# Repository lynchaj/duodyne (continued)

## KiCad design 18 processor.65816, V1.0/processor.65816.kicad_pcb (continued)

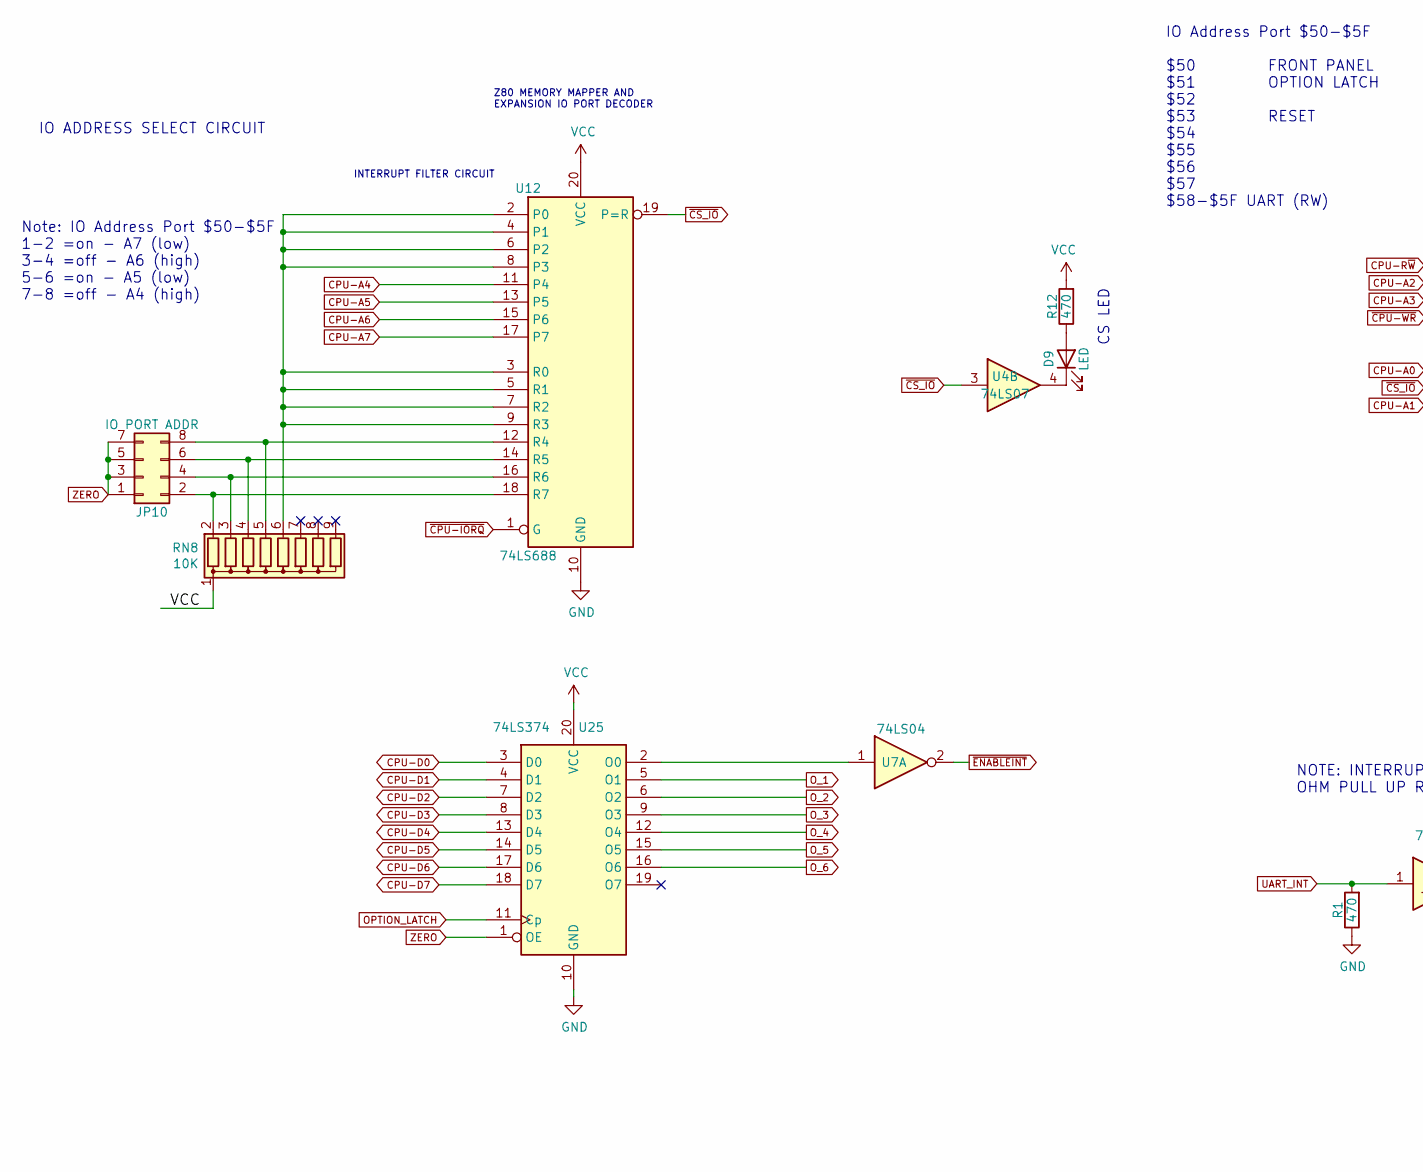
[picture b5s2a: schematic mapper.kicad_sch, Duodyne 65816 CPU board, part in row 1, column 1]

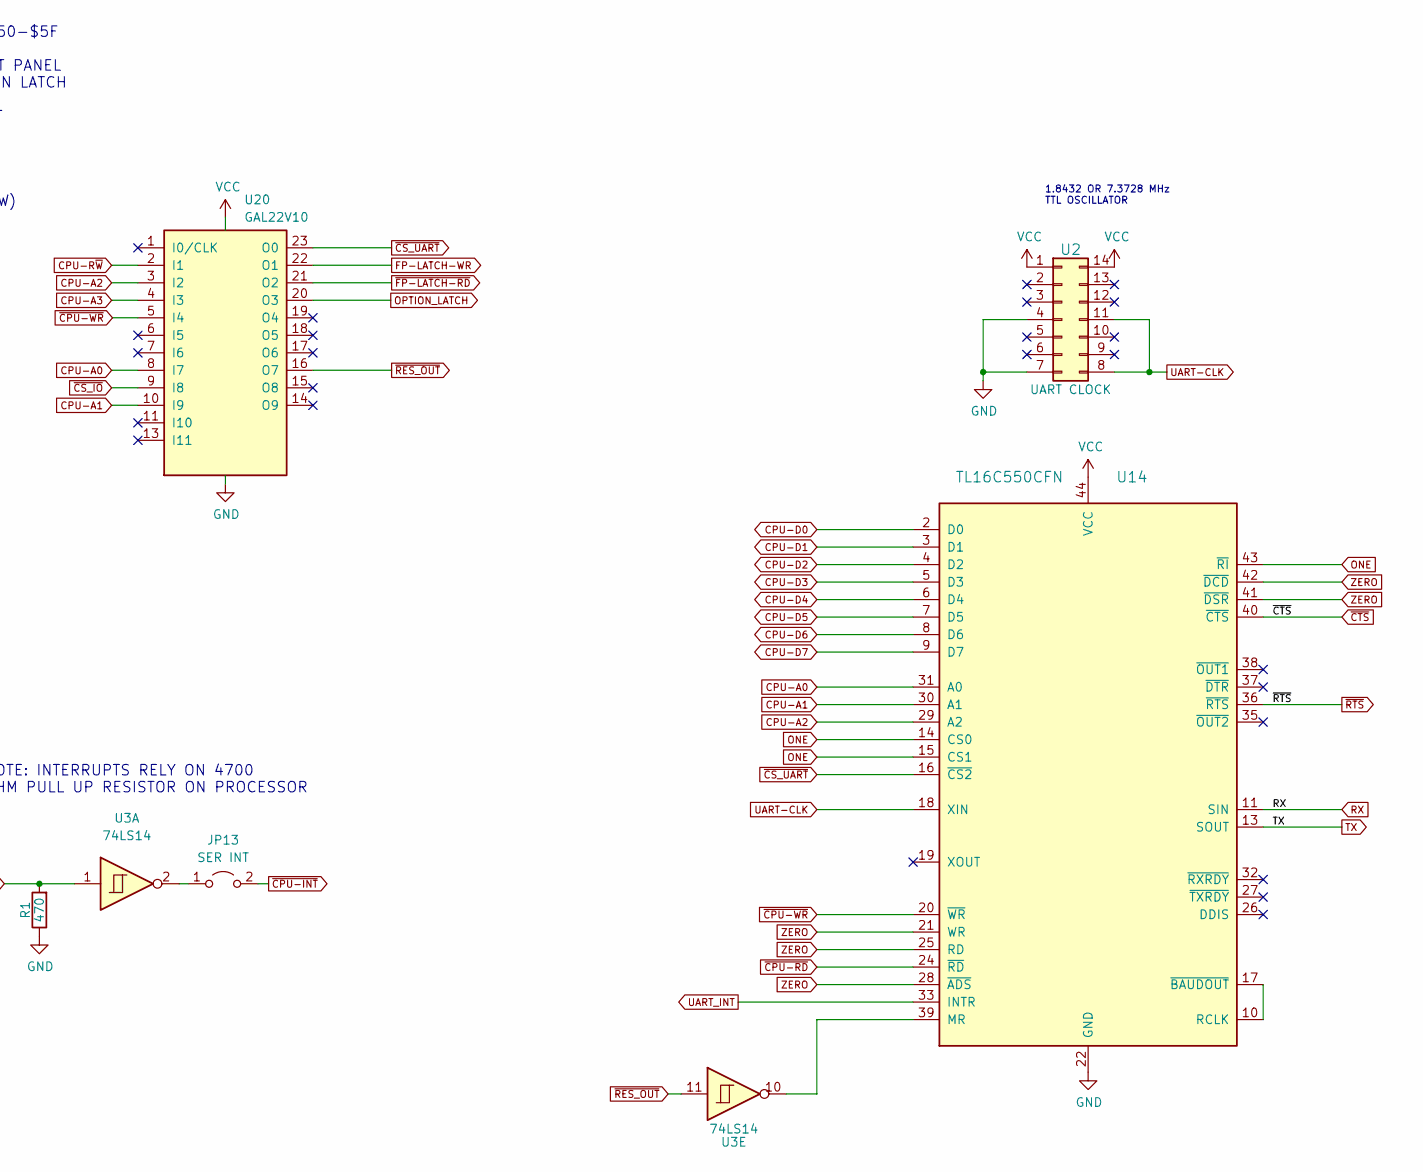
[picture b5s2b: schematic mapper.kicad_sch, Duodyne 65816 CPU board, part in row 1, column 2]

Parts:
D9: LED; LED_D3.0mm_Horizontal_O3.81mm_Z2.0mm
JP10: IO PORT ADDR; PinHeader_2x04_P2.54mm_Vertical
JP13: SER INT; PinHeader_1x02_P2.54mm_Vertical
R1, R12: 470; R_Axial_DIN0207_L6.3mm_D2.5mm_P7.62mm_Horizontal
RN8: 10K; R_Array_SIP9
U2: UART CLOCK; DIP-14_W7.62mm_Socket_LongPads
U3: 74LS14; DIP-14_W7.62mm_Socket_LongPads
U4: 74LS07; DIP-14_W7.62mm_Socket_LongPads
U7: 74LS04; DIP-14_W7.62mm_Socket_LongPads
U12: 74LS688; DIP-20_W7.62mm_Socket_LongPads
U14: TL16C550CFN; PLCC-44_THT-Socket
U20: GAL22V10; DIP-24_W7.62mm_Socket_LongPads
U25: 74LS374; DIP-20_W7.62mm_Socket_LongPads

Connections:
CPU-A0: U14.31 (A0), U20.8 (I7); also elsewhere on the board
CPU-A1: U14.30 (A1), U20.10 (I9); also elsewhere on the board
CPU-A2: U14.29 (A2), U20.3 (I2); also elsewhere on the board
CPU-A3: U20.4 (I3); also elsewhere on the board
CPU-A4: U12.11 (P4); also elsewhere on the board
CPU-A5: U12.13 (P5); also elsewhere on the board
CPU-A6: U12.15 (P6); also elsewhere on the board
CPU-A7: U12.17 (P7); also elsewhere on the board
CPU-D0: U14.2 (D0), U25.3 (D0); also elsewhere on the board
CPU-D1: U14.3 (D1), U25.4 (D1); also elsewhere on the board
CPU-D2: U14.4 (D2), U25.7 (D2); also elsewhere on the board
CPU-D3: U14.5 (D3), U25.8 (D3); also elsewhere on the board
CPU-D4: U14.6 (D4), U25.13 (D4); also elsewhere on the board
CPU-D5: U14.7 (D5), U25.14 (D5); also elsewhere on the board
CPU-D6: U14.8 (D6), U25.17 (D6); also elsewhere on the board
CPU-D7: U14.9 (D7), U25.18 (D7); also elsewhere on the board
CPU-R~W: U20.2 (I1); also elsewhere on the board
FP-LATCH-WR: U20.22 (O1); also elsewhere on the board
GND: R1.1, U2.4, U2.7, U12.10 (GND), U14.22 (GND), U20.12 (GND), U25.10 (GND); also elsewhere on the board
unnamed: D9.1 (K), U4.4
unnamed: D9.2 (A), R12.1
unnamed: JP10.2, RN8.2 (R1), U12.18 (R7)
unnamed: JP10.4, RN8.3 (R2), U12.16 (R6)
unnamed: JP10.6, RN8.4 (R3), U12.14 (R5)
unnamed: JP10.8, RN8.5 (R4), U12.12 (R4)
unnamed: JP13.1 (A), U3.2
unnamed: RN8.6 (R5), U12.2 (P0), U12.3 (R0), U12.4 (P1), U12.5 (R1), U12.6 (P2), U12.7 (R2), U12.8 (P3), U12.9 (R3)
unnamed: U14.10 (RCLK), U14.17 (~BAUDOUT)
unnamed: U3.10, U14.39 (MR)
unnamed: U7.1, U25.2 (O0)
ONE: U14.14 (CS0), U14.15 (CS1), U14.43 (~RI); also elsewhere on the board
OPTION_LATCH: U20.20 (O3), U25.11 (Cp)
O_1: U25.5 (O1); also elsewhere on the board
O_2: U25.6 (O2); also elsewhere on the board
O_3: U25.9 (O3); also elsewhere on the board
O_4: U25.12 (O4); also elsewhere on the board
O_5: U25.15 (O5); also elsewhere on the board
O_6: U25.16 (O6); also elsewhere on the board
RX: U14.11 (SIN); also elsewhere on the board
TX: U14.13 (SOUT); also elsewhere on the board
UART-CLK: U2.8, U2.11, U14.18 (XIN)
UART_INT: R1.2, U3.1, U14.33 (INTR)
VCC: R12.2, RN8.1 (common), U2.1, U2.14, U12.20 (VCC), U14.44 (VCC), U20.24 (VCC), U25.20 (VCC); also elsewhere on the board
ZERO: JP10.1, JP10.3, JP10.5, JP10.7, U14.21 (WR), U14.25 (RD), U14.28 (~ADS), U14.41 (~DSR), U14.42 (~DCD), U25.1 (OE); also elsewhere on the board
~CPU-INT: JP13.2 (B); also elsewhere on the board
~CPU-IORQ: U12.1 (G); also elsewhere on the board
~CPU-RD: U14.24 (~RD); also elsewhere on the board
~CPU-WR: U14.20 (~WR), U20.5 (I4); also elsewhere on the board
~CS_IO: U4.3, U12.19 (P=R), U20.9 (I8); also elsewhere on the board
~CS_UART: U14.16 (~CS2), U20.23 (O0)
~CTS: U14.40 (~CTS); also elsewhere on the board
~ENABLEINT: U7.2; also elsewhere on the board
~FP-LATCH-RD: U20.21 (O2); also elsewhere on the board
~RES_OUT: U3.11, U20.16 (O7); also elsewhere on the board
~RTS: U14.36 (~RTS); also elsewhere on the board

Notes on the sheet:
Z80 MEMORY MAPPER AND EXPANSION IO PORT DECODER
CS LED
IO ADDRESS SELECT CIRCUIT
INTERRUPT FILTER CIRCUIT
1.8432 OR 7.3728 MHz TTL OSCILLATOR
IO Address Port $50-$5F $50 FRONT PANEL $51 OPTION LATCH $52 $53 RESET $54 $55 $56 $57 $58-$5F UART (RW)
NOTE: INTERRUPTS RELY ON 4700 OHM PULL UP RESISTOR ON PROCESSOR
Note: IO Address Port $50-$5F 1-2 =on - A7 (low) 3-4 =off - A6 (high) 5-6 =on - A5 (low) 7-8 =off - A4 (high)

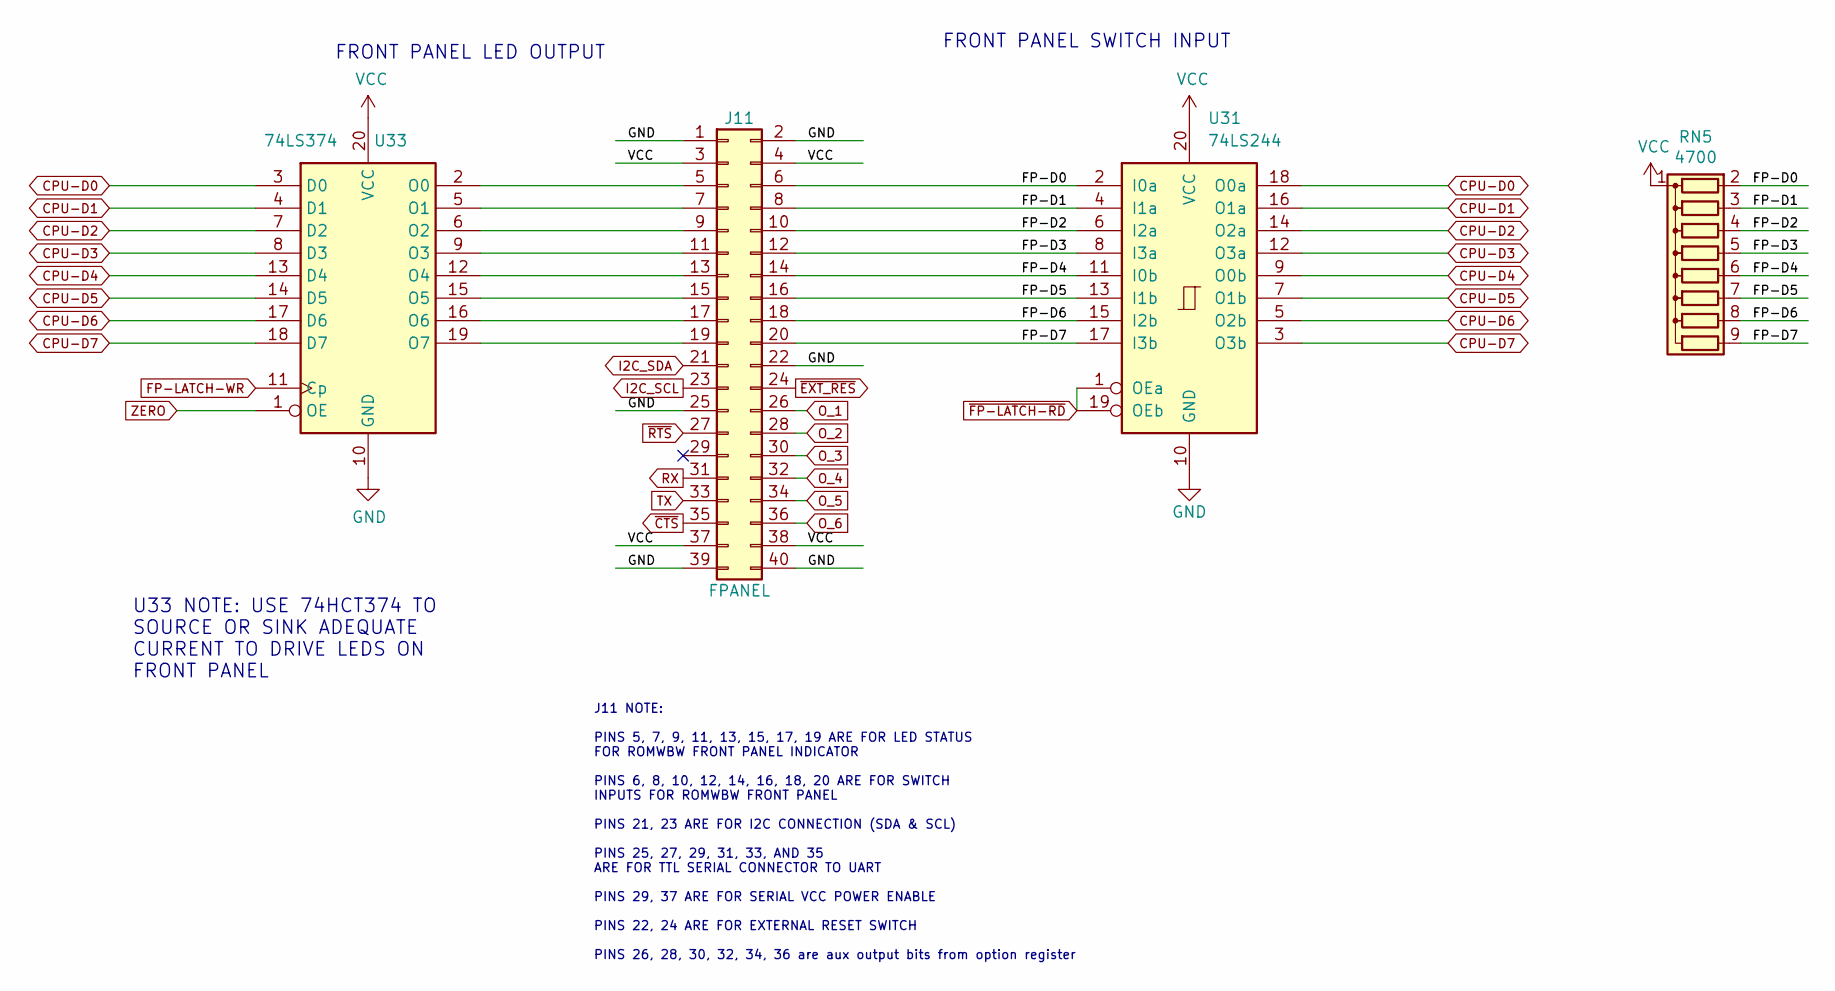
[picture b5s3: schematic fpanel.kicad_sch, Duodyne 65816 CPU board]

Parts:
J11: FPANEL; IDC-Header_2x20_P2.54mm_Horizontal
RN5: 4700; R_Array_SIP9
U31: 74LS244; DIP-20_W7.62mm_Socket_LongPads
U33: 74LS374; DIP-20_W7.62mm_Socket_LongPads

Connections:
/fpanel/FP-D0: J11.6, RN5.2 (R1), U31.2 (I0a)
/fpanel/FP-D1: J11.8, RN5.3 (R2), U31.4 (I1a)
/fpanel/FP-D2: J11.10, RN5.4 (R3), U31.6 (I2a)
/fpanel/FP-D3: J11.12, RN5.5 (R4), U31.8 (I3a)
/fpanel/FP-D4: J11.14, RN5.6 (R5), U31.11 (I0b)
/fpanel/FP-D5: J11.16, RN5.7 (R6), U31.13 (I1b)
/fpanel/FP-D6: J11.18, RN5.8 (R7), U31.15 (I2b)
/fpanel/FP-D7: J11.20, RN5.9 (R8), U31.17 (I3b)
CPU-D0: U31.18 (O0a), U33.3 (D0); also elsewhere on the board
CPU-D1: U31.16 (O1a), U33.4 (D1); also elsewhere on the board
CPU-D2: U31.14 (O2a), U33.7 (D2); also elsewhere on the board
CPU-D3: U31.12 (O3a), U33.8 (D3); also elsewhere on the board
CPU-D4: U31.9 (O0b), U33.13 (D4); also elsewhere on the board
CPU-D5: U31.7 (O1b), U33.14 (D5); also elsewhere on the board
CPU-D6: U31.5 (O2b), U33.17 (D6); also elsewhere on the board
CPU-D7: U31.3 (O3b), U33.18 (D7); also elsewhere on the board
FP-LATCH-WR: U33.11 (Cp); also elsewhere on the board
GND: J11.1, J11.2, J11.22, J11.25, J11.39, J11.40, U31.10 (GND), U33.10 (GND); also elsewhere on the board
I2C_SCL: J11.23; also elsewhere on the board
I2C_SDA: J11.21; also elsewhere on the board
unnamed: J11.5, U33.2 (O0)
unnamed: J11.7, U33.5 (O1)
unnamed: J11.9, U33.6 (O2)
unnamed: J11.11, U33.9 (O3)
unnamed: J11.13, U33.12 (O4)
unnamed: J11.15, U33.15 (O5)
unnamed: J11.17, U33.16 (O6)
unnamed: J11.19, U33.19 (O7)
O_1: J11.26; also elsewhere on the board
O_2: J11.28; also elsewhere on the board
O_3: J11.30; also elsewhere on the board
O_4: J11.32; also elsewhere on the board
O_5: J11.34; also elsewhere on the board
O_6: J11.36; also elsewhere on the board
RX: J11.31; also elsewhere on the board
TX: J11.33; also elsewhere on the board
VCC: J11.3, J11.4, J11.37, J11.38, RN5.1 (common), U31.20 (VCC), U33.20 (VCC); also elsewhere on the board
ZERO: U33.1 (OE); also elsewhere on the board
~CTS: J11.35; also elsewhere on the board
~EXT_RES: J11.24; also elsewhere on the board
~FP-LATCH-RD: U31.1 (OEa), U31.19 (OEb); also elsewhere on the board
~RTS: J11.27; also elsewhere on the board

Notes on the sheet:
J11 NOTE: PINS 5, 7, 9, 11, 13, 15, 17, 19 ARE FOR LED STATUS FOR ROMWBW FRONT PANEL INDICATOR PINS 6, 8, 10, 12, 14, 16, 18, 20 ARE FOR SWITCH INPUTS FOR ROMWBW FRONT PANEL PINS 21, 23 ARE FOR I2C CONNECTION (SDA & SCL) PINS 25, 27, 29, 31, 33, AND 35 ARE FOR TTL SERIAL CONNECTOR TO UART PINS 29, 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
U33 NOTE: USE 74HCT374 TO SOURCE OR SINK ADEQUATE CURRENT TO DRIVE LEDS ON FRONT PANEL
FRONT PANEL SWITCH INPUT
FRONT PANEL LED OUTPUT

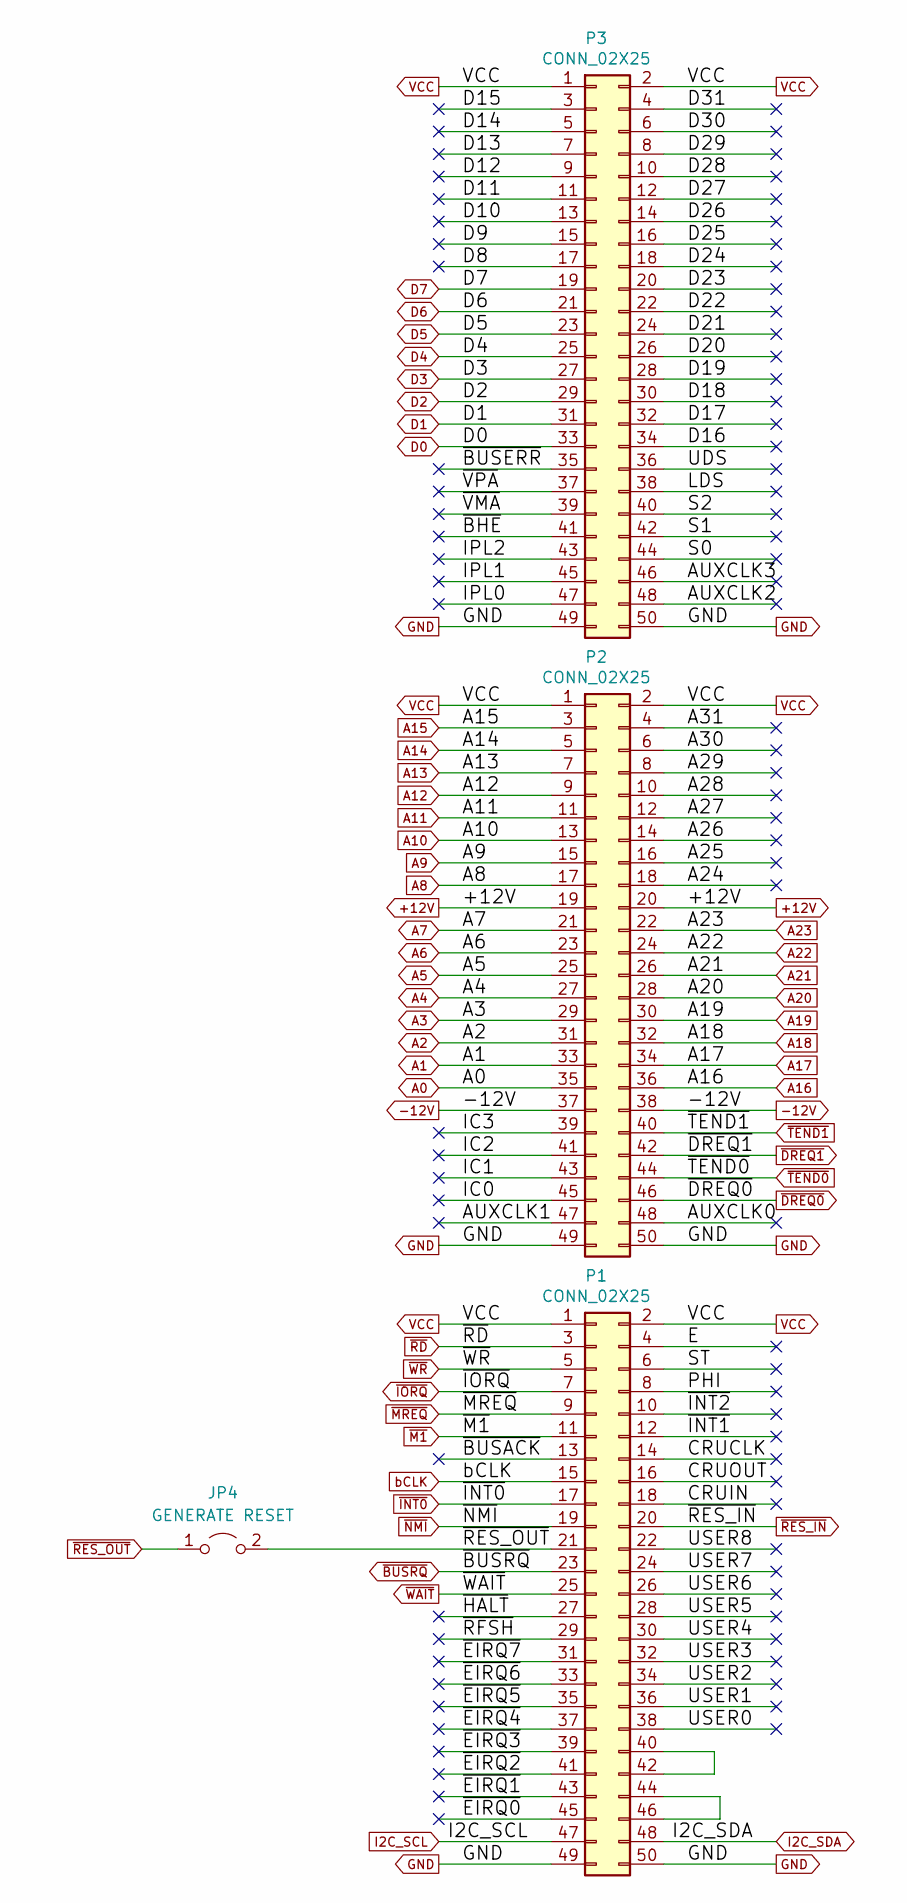
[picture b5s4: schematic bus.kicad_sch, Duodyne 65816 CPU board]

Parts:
JP4: GENERATE RESET; PinHeader_1x02_P2.54mm_Horizontal
P1, P2, P3: CONN_02X25; IDC-Header_2x25_P2.54mm_Horizontal

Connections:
+12V: P2.19, P2.20
-12V: P2.37, P2.38
/bus/A24: P2.18
/bus/A25: P2.16
/bus/A26: P2.14
/bus/A27: P2.12
/bus/A28: P2.10
/bus/A29: P2.8
/bus/A30: P2.6
/bus/A31: P2.4
/bus/AUXCLK0: P2.48
/bus/AUXCLK1: P2.47
/bus/AUXCLK2: P3.48
/bus/AUXCLK3: P3.46
/bus/CRUCLK: P1.14
/bus/CRUIN: P1.18
/bus/CRUOUT: P1.16
/bus/D8: P3.17
/bus/D9: P3.15
/bus/D10: P3.13
/bus/D11: P3.11
/bus/D12: P3.9
/bus/D13: P3.7
/bus/D14: P3.5
/bus/D15: P3.3
/bus/D16: P3.34
/bus/D17: P3.32
/bus/D18: P3.30
/bus/D19: P3.28
/bus/D20: P3.26
/bus/D21: P3.24
/bus/D22: P3.22
/bus/D23: P3.20
/bus/D24: P3.18
/bus/D25: P3.16
/bus/D26: P3.14
/bus/D27: P3.12
/bus/D28: P3.10
/bus/D29: P3.8
/bus/D30: P3.6
/bus/D31: P3.4
/bus/E: P1.4
/bus/IC0: P2.45
/bus/IC1: P2.43
/bus/IC2: P2.41
/bus/IC3: P2.39
/bus/IPL0: P3.47
/bus/IPL1: P3.45
/bus/IPL2: P3.43
/bus/LDS: P3.38
/bus/PHI: P1.8
/bus/S0: P3.44
/bus/S1: P3.42
/bus/S2: P3.40
/bus/ST: P1.6
/bus/UDS: P3.36
/bus/USER0: P1.38
/bus/USER1: P1.36
/bus/USER2: P1.34
/bus/USER3: P1.32
/bus/USER4: P1.30
/bus/USER5: P1.28
/bus/USER6: P1.26
/bus/USER7: P1.24
/bus/USER8: P1.22
/bus/~BHE: P3.41
/bus/~BUSACK: P1.13
/bus/~BUSERR: P3.35
/bus/~EIRQ0: P1.45
/bus/~EIRQ1: P1.43
/bus/~EIRQ2: P1.41
/bus/~EIRQ3: P1.39
/bus/~EIRQ4: P1.37
/bus/~EIRQ5: P1.35
/bus/~EIRQ6: P1.33
/bus/~EIRQ7: P1.31
/bus/~HALT: P1.27
/bus/~INT1: P1.12
/bus/~INT2: P1.10
/bus/~RFSH: P1.29
/bus/~VMA: P3.39
/bus/~VPA: P3.37
A0: P2.35; also elsewhere on the board
A1: P2.33; also elsewhere on the board
A2: P2.31; also elsewhere on the board
A3: P2.29; also elsewhere on the board
A4: P2.27; also elsewhere on the board
A5: P2.25; also elsewhere on the board
A6: P2.23; also elsewhere on the board
A7: P2.21; also elsewhere on the board
A8: P2.17; also elsewhere on the board
A9: P2.15; also elsewhere on the board
A10: P2.13; also elsewhere on the board
A11: P2.11; also elsewhere on the board
A12: P2.9; also elsewhere on the board
A13: P2.7; also elsewhere on the board
A14: P2.5; also elsewhere on the board
A15: P2.3; also elsewhere on the board
A16: P2.36; also elsewhere on the board
A17: P2.34; also elsewhere on the board
A18: P2.32; also elsewhere on the board
A19: P2.30; also elsewhere on the board
A20: P2.28; also elsewhere on the board
A21: P2.26; also elsewhere on the board
A22: P2.24; also elsewhere on the board
A23: P2.22; also elsewhere on the board
D0: P3.33; also elsewhere on the board
D1: P3.31; also elsewhere on the board
D2: P3.29; also elsewhere on the board
D3: P3.27; also elsewhere on the board
D4: P3.25; also elsewhere on the board
D5: P3.23; also elsewhere on the board
D6: P3.21; also elsewhere on the board
D7: P3.19; also elsewhere on the board
GND: P1.49, P1.50, P2.49, P2.50, P3.49, P3.50; also elsewhere on the board
I2C_SCL: P1.47; also elsewhere on the board
I2C_SDA: P1.48; also elsewhere on the board
unnamed: P1.40, P1.42
unnamed: P1.44, P1.46
VCC: P1.1, P1.2, P2.1, P2.2, P3.1, P3.2; also elsewhere on the board
bCLK: P1.15; also elsewhere on the board
~BUSRQ: P1.23; also elsewhere on the board
~DREQ0: P2.46; also elsewhere on the board
~DREQ1: P2.42; also elsewhere on the board
~INT0: P1.17; also elsewhere on the board
~IORQ: P1.7; also elsewhere on the board
~M1: P1.11; also elsewhere on the board
~MREQ: P1.9; also elsewhere on the board
~NMI: P1.19; also elsewhere on the board
~RD: P1.3; also elsewhere on the board
~RES_IN: P1.20; also elsewhere on the board
~RES_OUT: JP4.1 (A), JP4.2 (B), P1.21; also elsewhere on the board
~TEND0: P2.44; also elsewhere on the board
~TEND1: P2.40; also elsewhere on the board
~WAIT: P1.25; also elsewhere on the board
~WR: P1.5; also elsewhere on the board

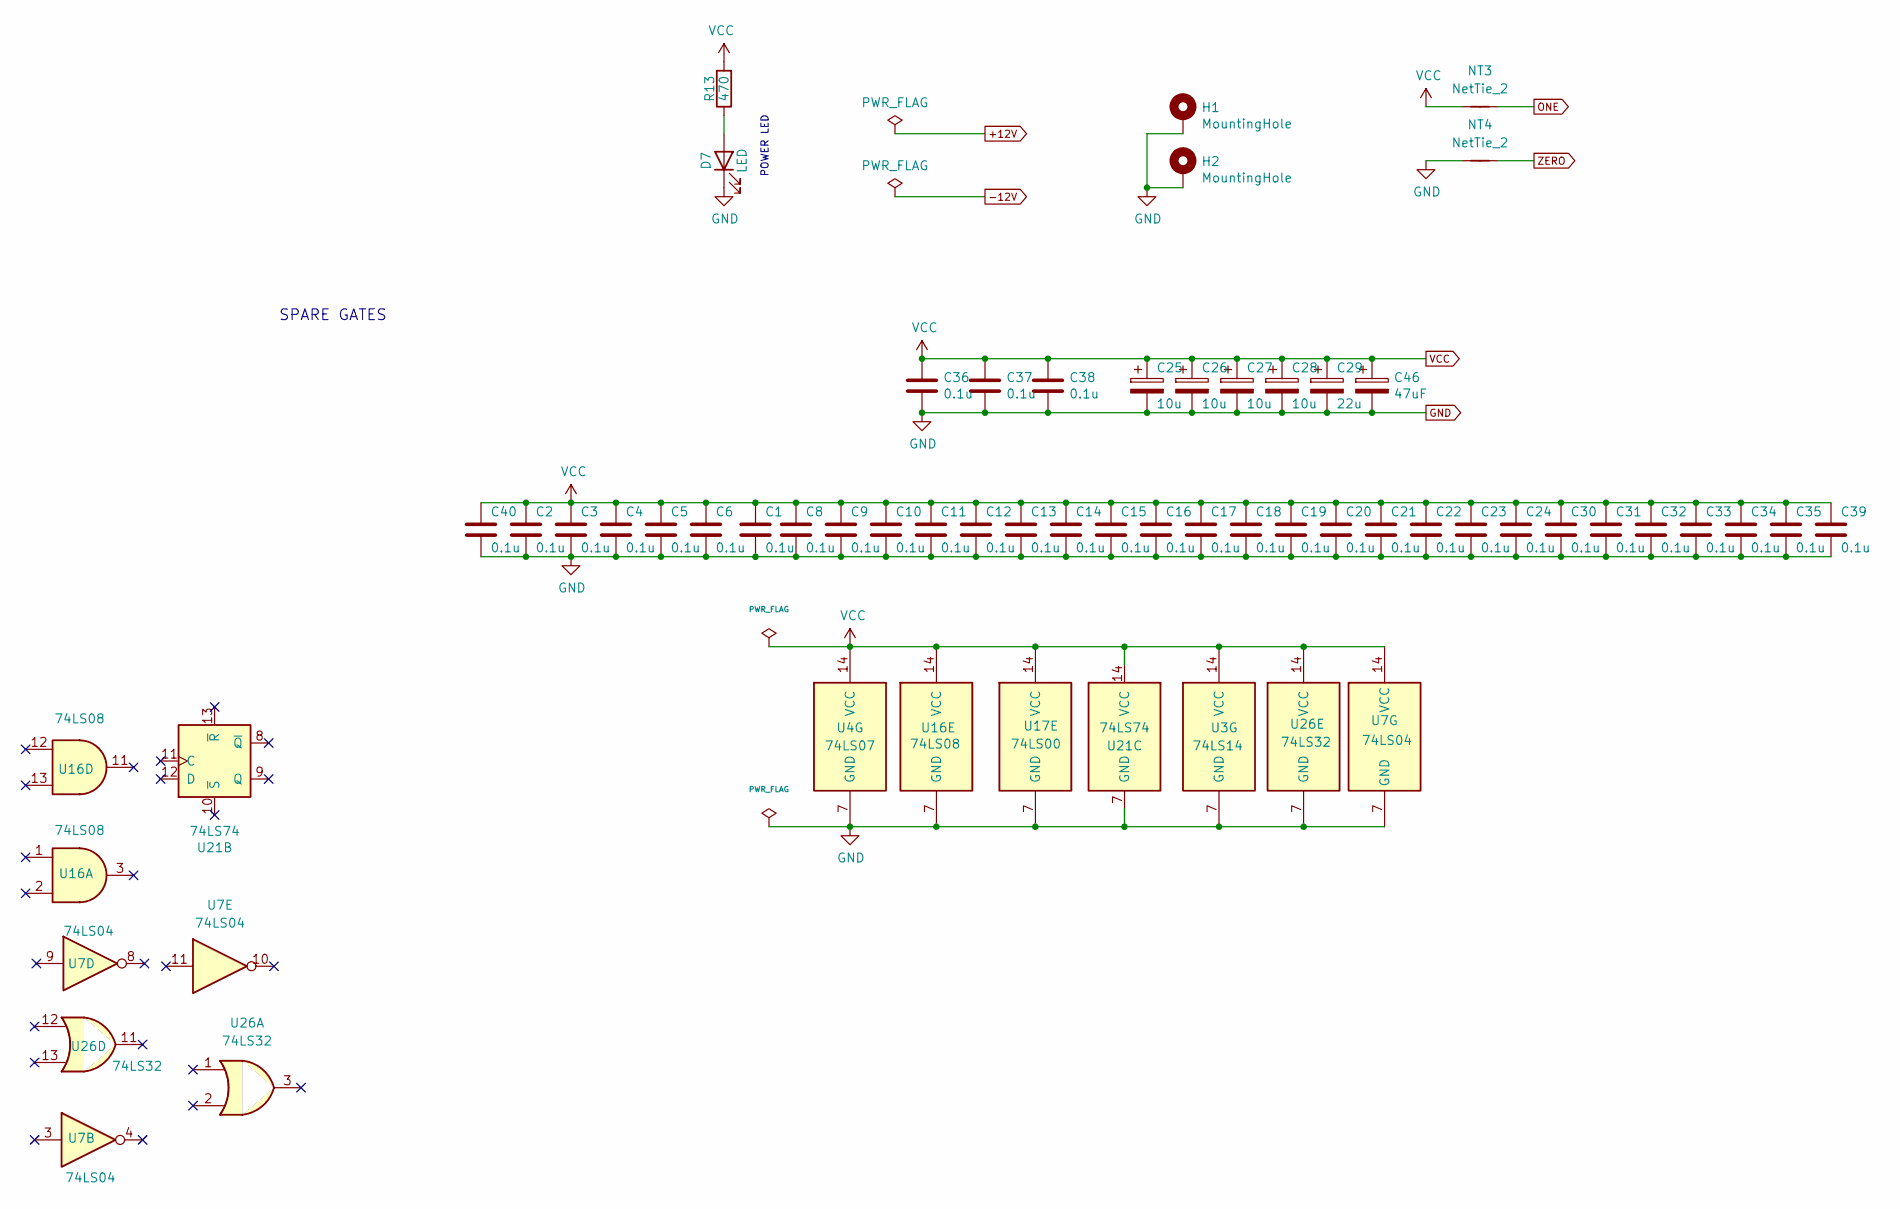
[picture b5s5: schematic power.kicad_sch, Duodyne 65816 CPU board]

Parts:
C1, C2, C3, C4, C5, C6, C8, C9, C10, C11, C12, C13, C14, C15, C16, C17, C18, C19, C20, C21, C22, C23, C24, C30, C31, C32, C33, C34, C35, C36, C37, C38, C39, C40: 0.1u; C_Disc_D5.0mm_W2.5mm_P5.00mm
C25, C26, C27, C28: 10u; CP_Radial_D5.0mm_P2.50mm
C29: 22u; CP_Radial_D5.0mm_P2.50mm
C46: 47uF; CP_Radial_D5.0mm_P2.50mm
D7: LED; LED_D3.0mm_Horizontal_O3.81mm_Z2.0mm
H1, H2: MountingHole; MountingHole_3.2mm_M3_Pad
NT3, NT4: NetTie_2; NetTie-2_THT_Pad0.3mm
R13: 470; R_Axial_DIN0207_L6.3mm_D2.5mm_P7.62mm_Horizontal
U3: 74LS14; DIP-14_W7.62mm_Socket_LongPads
U4: 74LS07; DIP-14_W7.62mm_Socket_LongPads
U7: 74LS04; DIP-14_W7.62mm_Socket_LongPads
U16: 74LS08; DIP-14_W7.62mm_Socket_LongPads
U17: 74LS00; DIP-14_W7.62mm_Socket_LongPads
U21: 74LS74; DIP-14_W7.62mm_Socket_LongPads
U26: 74LS32; DIP-14_W7.62mm_Socket_LongPads

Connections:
GND: C1.2, C2.2, C3.2, C4.2, C5.2, C6.2, C8.2, C9.2, C10.2, C11.2, C12.2, C13.2, C14.2, C15.2, C16.2, C17.2, C18.2, C19.2, C20.2, C21.2, C22.2, C23.2, C24.2, C25.2, C26.2, C27.2, C28.2, C29.2, C30.2, C31.2, C32.2, C33.2, C34.2, C35.2, C36.2, C37.2, C38.2, C39.2, C40.2, C46.2, D7.1 (K), H1.1, H2.1, NT4.1, U3.7 (GND), U4.7 (GND), U7.7 (GND), U16.7 (GND), U17.7 (GND), U21.7 (GND), U26.7 (GND); also elsewhere on the board
unnamed: D7.2 (A), R13.1
ONE: NT3.2; also elsewhere on the board
VCC: C1.1, C2.1, C3.1, C4.1, C5.1, C6.1, C8.1, C9.1, C10.1, C11.1, C12.1, C13.1, C14.1, C15.1, C16.1, C17.1, C18.1, C19.1, C20.1, C21.1, C22.1, C23.1, C24.1, C25.1, C26.1, C27.1, C28.1, C29.1, C30.1, C31.1, C32.1, C33.1, C34.1, C35.1, C36.1, C37.1, C38.1, C39.1, C40.1, C46.1, NT3.1, R13.2, U3.14 (VCC), U4.14 (VCC), U7.14 (VCC), U16.14 (VCC), U17.14 (VCC), U21.14 (VCC), U26.14 (VCC); also elsewhere on the board
ZERO: NT4.2; also elsewhere on the board

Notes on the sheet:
POWER LED
SPARE GATES
